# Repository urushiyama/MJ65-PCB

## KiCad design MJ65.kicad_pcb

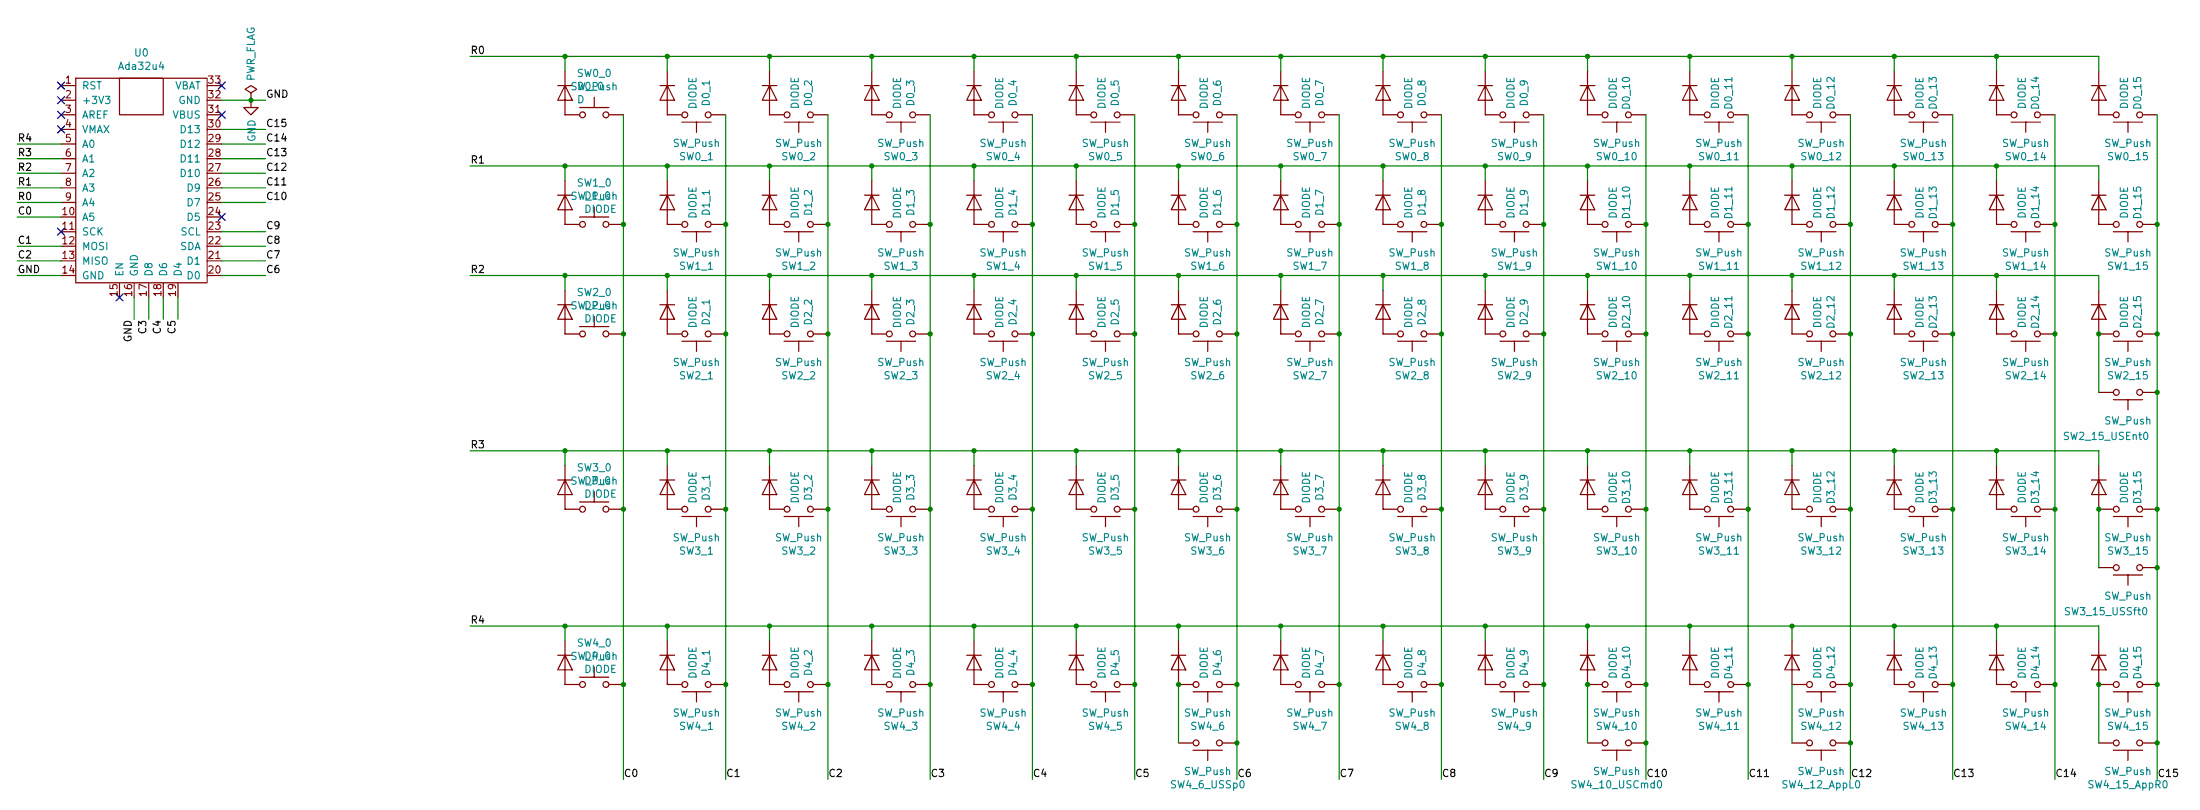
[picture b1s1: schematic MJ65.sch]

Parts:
D0_0: D; Diode-dual
D0_1, D0_2, D0_3, D0_4, D0_5, D0_6, D0_7, D0_8, D0_9, D0_10, D0_11, D0_12, D0_13, D0_14, D0_15, D1_0, D1_1, D1_2, D1_3, D1_4, D1_5, D1_6, D1_7, D1_8, D1_9, D1_10, D1_11, D1_12, D1_13, D1_14, D1_15, D2_0, D2_1, D2_2, D2_3, D2_4, D2_5, D2_6, D2_7, D2_8, D2_9, D2_10, D2_11, D2_12, D2_13, D2_14, D2_15, D3_0, D3_1, D3_2, D3_3, D3_4, D3_5, D3_6, D3_7, D3_8, D3_9, D3_10, D3_11, D3_12, D3_13, D3_14, D3_15, D4_0, D4_1, D4_2, D4_3, D4_4, D4_5, D4_6, D4_7, D4_8, D4_9, D4_10, D4_11, D4_12, D4_13, D4_14, D4_15: DIODE; Diode-dual
SW0_0, SW1_0, SW1_14, SW2_0, SW2_14, SW3_0, SW3_13, SW3_14, SW4_0, SW4_9, SW4_13: SW_Push; Triple_PCB_100H-External-Switch-Pad
SW0_1, SW0_2, SW0_3, SW0_4, SW0_5, SW0_6, SW0_7, SW0_8, SW0_9, SW0_10, SW0_11, SW0_12, SW0_13, SW0_14, SW0_15, SW1_2, SW1_3, SW1_4, SW1_5, SW1_6, SW1_7, SW1_8, SW1_9, SW1_10, SW1_11, SW1_12, SW1_13, SW2_2, SW2_3, SW2_4, SW2_5, SW2_6, SW2_7, SW2_8, SW2_9, SW2_10, SW2_11, SW2_12, SW2_13, SW3_2, SW3_3, SW3_4, SW3_5, SW3_6, SW3_7, SW3_8, SW3_9, SW3_10, SW3_11, SW3_12, SW4_2, SW4_6, SW4_10_USCmd0, SW4_11, SW4_12_AppL0, SW4_14, SW4_15_AppR0: SW_Push; Triple_PCB_100H
SW1_1, SW1_15, SW4_1, SW4_12, SW4_15: SW_Push; Triple_PCB_150H
SW2_1, SW3_15, SW4_5, SW4_7: SW_Push; Triple_PCB_175H
SW2_15: SW_Push; Triple_PCB_200V
SW2_15_USEnt0, SW3_1: SW_Push; Triple_PCB_225H
SW3_15_USSft0: SW_Push; Triple_PCB_275H-v-flip
SW4_3, SW4_4, SW4_8, SW4_10: SW_Push; Triple_PCB_125H
SW4_6_USSp0: SW_Push; Triple_PCB_625H-v-flip
U0: Ada32u4

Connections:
/C0: SW0_0.1, SW1_0.1, SW2_0.1, SW3_0.1, SW4_0.1, U0.10 (A5)
/C1: SW0_1.2, SW1_1.2, SW2_1.2, SW3_1.2, SW4_1.2, U0.12 (MOSI)
/C2: SW0_2.2, SW1_2.2, SW2_2.2, SW3_2.2, SW4_2.2, U0.13 (MISO)
/C3: SW0_3.2, SW1_3.2, SW2_3.2, SW3_3.2, SW4_3.2, U0.17 (D8)
/C4: SW0_4.2, SW1_4.2, SW2_4.2, SW3_4.2, SW4_4.2, U0.18 (D6)
/C5: SW0_5.2, SW1_5.2, SW2_5.2, SW3_5.2, SW4_5.2, U0.19 (D4)
/C6: SW0_6.2, SW1_6.2, SW2_6.2, SW3_6.2, SW4_6.2, SW4_6_USSp0.2, U0.20 (D0)
/C7: SW0_7.2, SW1_7.2, SW2_7.2, SW3_7.2, SW4_7.2, U0.21 (D1)
/C8: SW0_8.2, SW1_8.2, SW2_8.2, SW3_8.2, SW4_8.2, U0.22 (SDA)
/C9: SW0_9.2, SW1_9.2, SW2_9.2, SW3_9.2, SW4_9.2, U0.23 (SCL)
/C10: SW0_10.2, SW1_10.2, SW2_10.2, SW3_10.2, SW4_10.2, SW4_10_USCmd0.2, U0.25 (D7)
/C11: SW0_11.2, SW1_11.2, SW2_11.2, SW3_11.2, SW4_11.2, U0.26 (D9)
/C12: SW0_12.2, SW1_12.2, SW2_12.2, SW3_12.2, SW4_12.2, SW4_12_AppL0.2, U0.27 (D10)
/C13: SW0_13.2, SW1_13.2, SW2_13.2, SW3_13.2, SW4_13.2, U0.28 (D11)
/C14: SW0_14.2, SW1_14.2, SW2_14.2, SW3_14.2, SW4_14.2, U0.29 (D12)
/C15: SW0_15.2, SW1_15.2, SW2_15.2, SW2_15_USEnt0.2, SW3_15.2, SW3_15_USSft0.2, SW4_15.2, SW4_15_AppR0.2, U0.30 (D13)
/R0: D0_0.1 (K), D0_1.1 (K), D0_2.1 (K), D0_3.1 (K), D0_4.1 (K), D0_5.1 (K), D0_6.1 (K), D0_7.1 (K), D0_8.1 (K), D0_9.1 (K), D0_10.1 (K), D0_11.1 (K), D0_12.1 (K), D0_13.1 (K), D0_14.1 (K), D0_15.1 (K), U0.9 (A4)
/R1: D1_0.1 (K), D1_1.1 (K), D1_2.1 (K), D1_3.1 (K), D1_4.1 (K), D1_5.1 (K), D1_6.1 (K), D1_7.1 (K), D1_8.1 (K), D1_9.1 (K), D1_10.1 (K), D1_11.1 (K), D1_12.1 (K), D1_13.1 (K), D1_14.1 (K), D1_15.1 (K), U0.8 (A3)
/R2: D2_0.1 (K), D2_1.1 (K), D2_2.1 (K), D2_3.1 (K), D2_4.1 (K), D2_5.1 (K), D2_6.1 (K), D2_7.1 (K), D2_8.1 (K), D2_9.1 (K), D2_10.1 (K), D2_11.1 (K), D2_12.1 (K), D2_13.1 (K), D2_14.1 (K), D2_15.1 (K), U0.7 (A2)
/R3: D3_0.1 (K), D3_1.1 (K), D3_2.1 (K), D3_3.1 (K), D3_4.1 (K), D3_5.1 (K), D3_6.1 (K), D3_7.1 (K), D3_8.1 (K), D3_9.1 (K), D3_10.1 (K), D3_11.1 (K), D3_12.1 (K), D3_13.1 (K), D3_14.1 (K), D3_15.1 (K), U0.6 (A1)
/R4: D4_0.1 (K), D4_1.1 (K), D4_2.1 (K), D4_3.1 (K), D4_4.1 (K), D4_5.1 (K), D4_6.1 (K), D4_7.1 (K), D4_8.1 (K), D4_9.1 (K), D4_10.1 (K), D4_11.1 (K), D4_12.1 (K), D4_13.1 (K), D4_14.1 (K), D4_15.1 (K), U0.5 (A0)
GND: U0.14 (GND), U0.16 (GND), U0.32 (GND)
unnamed: D0_0.2 (A), SW0_0.2
unnamed: D0_1.2 (A), SW0_1.1
unnamed: D0_2.2 (A), SW0_2.1
unnamed: D0_3.2 (A), SW0_3.1
unnamed: D0_4.2 (A), SW0_4.1
unnamed: D0_5.2 (A), SW0_5.1
unnamed: D0_6.2 (A), SW0_6.1
unnamed: D0_7.2 (A), SW0_7.1
unnamed: D0_8.2 (A), SW0_8.1
unnamed: D0_9.2 (A), SW0_9.1
unnamed: D0_10.2 (A), SW0_10.1
unnamed: D0_11.2 (A), SW0_11.1
unnamed: D0_12.2 (A), SW0_12.1
unnamed: D0_13.2 (A), SW0_13.1
unnamed: D0_14.2 (A), SW0_14.1
unnamed: D0_15.2 (A), SW0_15.1
unnamed: D1_0.2 (A), SW1_0.2
unnamed: D1_1.2 (A), SW1_1.1
unnamed: D1_2.2 (A), SW1_2.1
unnamed: D1_3.2 (A), SW1_3.1
unnamed: D1_4.2 (A), SW1_4.1
unnamed: D1_5.2 (A), SW1_5.1
unnamed: D1_6.2 (A), SW1_6.1
unnamed: D1_7.2 (A), SW1_7.1
unnamed: D1_8.2 (A), SW1_8.1
unnamed: D1_9.2 (A), SW1_9.1
unnamed: D1_10.2 (A), SW1_10.1
unnamed: D1_11.2 (A), SW1_11.1
unnamed: D1_12.2 (A), SW1_12.1
unnamed: D1_13.2 (A), SW1_13.1
unnamed: D1_14.2 (A), SW1_14.1
unnamed: D1_15.2 (A), SW1_15.1
unnamed: D2_0.2 (A), SW2_0.2
unnamed: D2_1.2 (A), SW2_1.1
unnamed: D2_2.2 (A), SW2_2.1
unnamed: D2_3.2 (A), SW2_3.1
unnamed: D2_4.2 (A), SW2_4.1
unnamed: D2_5.2 (A), SW2_5.1
unnamed: D2_6.2 (A), SW2_6.1
unnamed: D2_7.2 (A), SW2_7.1
unnamed: D2_8.2 (A), SW2_8.1
unnamed: D2_9.2 (A), SW2_9.1
unnamed: D2_10.2 (A), SW2_10.1
unnamed: D2_11.2 (A), SW2_11.1
unnamed: D2_12.2 (A), SW2_12.1
unnamed: D2_13.2 (A), SW2_13.1
unnamed: D2_14.2 (A), SW2_14.1
unnamed: D2_15.2 (A), SW2_15.1, SW2_15_USEnt0.1
unnamed: D3_0.2 (A), SW3_0.2
unnamed: D3_1.2 (A), SW3_1.1
unnamed: D3_2.2 (A), SW3_2.1
unnamed: D3_3.2 (A), SW3_3.1
unnamed: D3_4.2 (A), SW3_4.1
unnamed: D3_5.2 (A), SW3_5.1
unnamed: D3_6.2 (A), SW3_6.1
unnamed: D3_7.2 (A), SW3_7.1
unnamed: D3_8.2 (A), SW3_8.1
unnamed: D3_9.2 (A), SW3_9.1
unnamed: D3_10.2 (A), SW3_10.1
unnamed: D3_11.2 (A), SW3_11.1
unnamed: D3_12.2 (A), SW3_12.1
unnamed: D3_13.2 (A), SW3_13.1
unnamed: D3_14.2 (A), SW3_14.1
unnamed: D3_15.2 (A), SW3_15.1, SW3_15_USSft0.1
unnamed: D4_0.2 (A), SW4_0.2
unnamed: D4_1.2 (A), SW4_1.1
unnamed: D4_2.2 (A), SW4_2.1
unnamed: D4_3.2 (A), SW4_3.1
unnamed: D4_4.2 (A), SW4_4.1
unnamed: D4_5.2 (A), SW4_5.1
unnamed: D4_6.2 (A), SW4_6.1, SW4_6_USSp0.1
unnamed: D4_7.2 (A), SW4_7.1
unnamed: D4_8.2 (A), SW4_8.1
unnamed: D4_9.2 (A), SW4_9.1
unnamed: D4_10.2 (A), SW4_10.1, SW4_10_USCmd0.1
unnamed: D4_11.2 (A), SW4_11.1
unnamed: D4_12.2 (A), SW4_12.1, SW4_12_AppL0.1
unnamed: D4_13.2 (A), SW4_13.1
unnamed: D4_14.2 (A), SW4_14.1
unnamed: D4_15.2 (A), SW4_15.1, SW4_15_AppR0.1

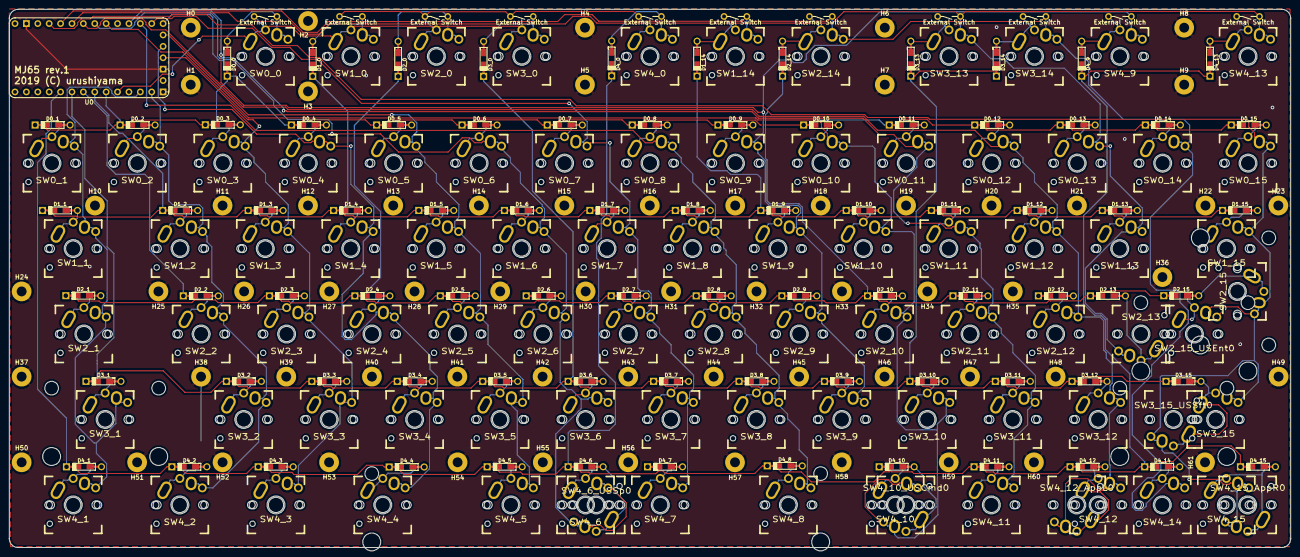
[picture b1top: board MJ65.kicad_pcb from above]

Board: 2 copper layers, 285.7 x 120.0 mm, 229 parts (0 on the bottom side), 102 nets.

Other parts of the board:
H0, H1, H2, H3, H4, H5, H6, H7, H8, H9, H10, H11, H12, H13, H14, H15, H16, H17, H18, H19, H20, H21, H22, H23, H24, H25, H26, H27, H28, H29, H30, H31, H32, H33, H34, H35, H36, H37, H38, H39, H40, H41, H42, H43, H44, H45, H46, H47, H48, H49, H50, H51, H52, H53, H54, H55, H56, H57, H58, H59, H60, H61: MountingHole_2.2mm_M2_Pad

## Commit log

2019-02-25 Add gitignore
2019-02-25 Created Footprint Layout
2019-02-26 Fix some route
2019-02-26 Add GND filling
2019-02-26 Tweak routes for larger GND filling
2019-02-26 Add rounded corner (2mm)
2019-02-27 Change footprint library to open source
2019-03-04 Tweak some wiring & ready to submission
2019-03-04 Fix library path from absolute to relative
2019-03-04 Remove unneeded wiring among GND mount holes
2019-03-09 Fix duplicated SW4_13
2019-03-09 Add MIT LICENSE
